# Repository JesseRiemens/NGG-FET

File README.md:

# NGG-FET
Wij gaan de NGG uit de labs in FET's bouwen

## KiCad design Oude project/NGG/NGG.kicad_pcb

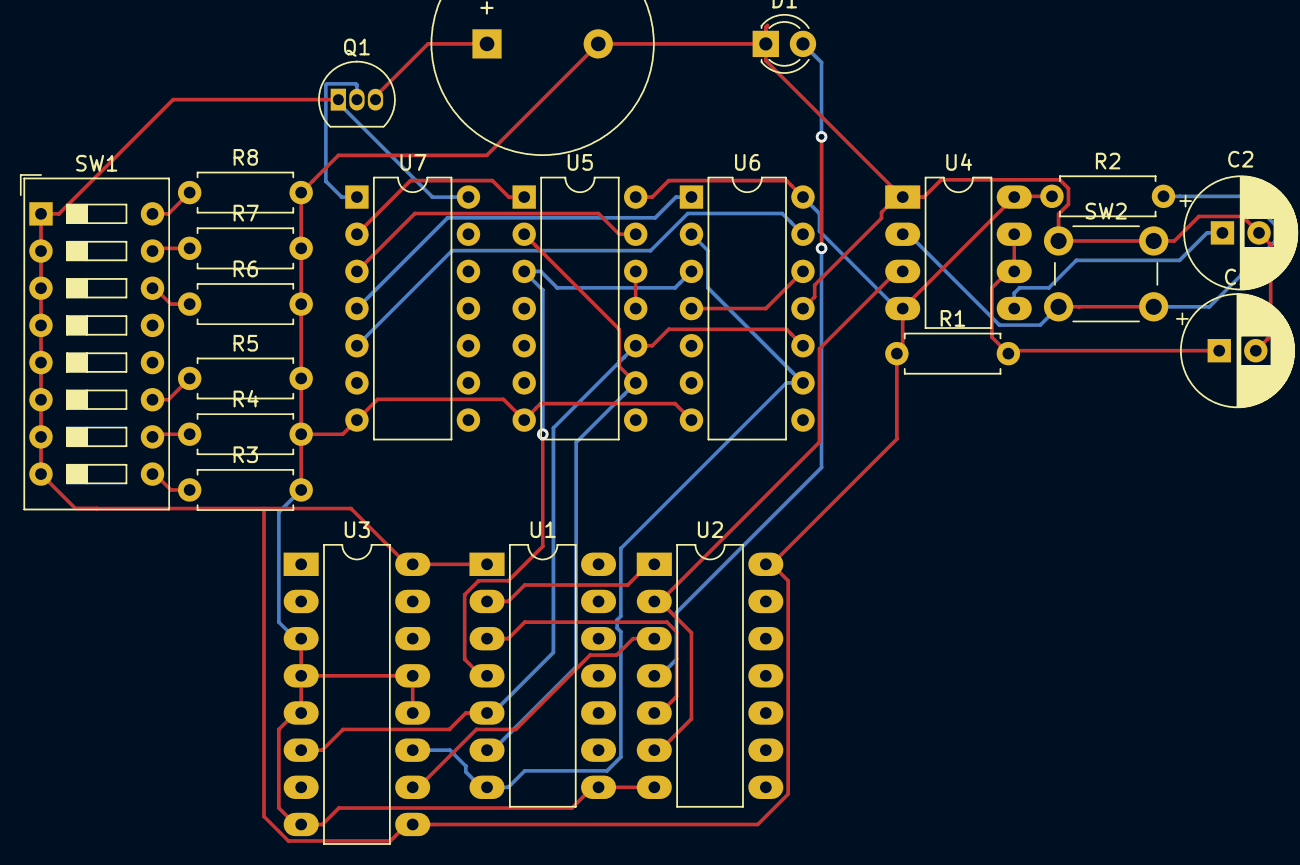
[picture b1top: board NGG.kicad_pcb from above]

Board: 2 copper layers, 22 parts (0 on the bottom side), 28 nets.

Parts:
BZ1: Buzzer; Buzzer_15x7.5RM7.6
C1: C; CP_Radial_D7.5mm_P2.50mm
C2: 10n; CP_Radial_D7.5mm_P2.50mm
D1: LED; LED_D3.0mm_Clear
Q1: BC547; TO-92_Inline
R1, R2: R; R_Axial_DIN0207_L6.3mm_D2.5mm_P7.62mm_Horizontal
R3, R4, R5, R6, R7, R8: 1k; R_Axial_DIN0207_L6.3mm_D2.5mm_P7.62mm_Horizontal
SW1: SW_DIP_x08; SW_DIP_SPSTx08_Slide_9.78x22.5mm_W7.62mm_P2.54mm
SW2: SW_Push; SW_PUSH_6mm
U1: 4049; DIP-14_W7.62mm_LongPads
U2: 4081; DIP-14_W7.62mm_LongPads
U3: 4029; DIP-16_W7.62mm_LongPads
U4: NE555; DIP-8_W7.62mm_LongPads
U5, U6: 4082; DIP-14_W7.62mm
U7: 4072; DIP-14_W7.62mm

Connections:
+5V: Q1.1, R1.1, R2.1, SW1.1, SW1.2, SW1.3, SW1.4, SW1.5, SW1.6, SW1.7, SW1.8, U1.1, U2.14, U3.9, U3.16, U4.4, U4.8, U5.14, U6.14, U7.14
/MUX/H: U6.4, U6.12
/MUX/M: U5.11, U5.12
/MUX/Mo: Q1.2, U7.1
/MUX/S0: U1.7, U3.11, U6.2, U6.9
/MUX/S1: U1.5, U3.6, U5.10, U6.10
/buzzer/BZ: BZ1.1, Q1.3
/comparator/A0: R6.1, SW1.14
/comparator/A1: R7.1, SW1.15
/comparator/A2: R8.1, SW1.16
/comparator/B0: R3.1, SW1.9
/comparator/B1: R4.1, SW1.10
/comparator/B2: R5.1, SW1.11
/comparator/EQ: U1.3, U2.5
/counter/E: U2.3, U3.10
/succesLED/L: D1.2, U2.4
/vergelijkknop/K: U2.2, U2.6, U4.3
GND: BZ1.2, C1.2, C2.2, D1.1, R3.2, R4.2, R5.2, R6.2, R7.2, R8.2, SW2.1, U1.8, U2.7, U3.3, U3.4, U3.5, U3.8, U3.12, U3.13, U4.1, U5.7, U6.7, U6.11, U7.7
unnamed: C1.1, R1.2, U4.6, U4.7
unnamed: C2.1, U4.5
unnamed: R2.2, SW2.2, U4.2
unnamed: U1.2, U2.1
unnamed: U1.4, U5.3, U6.3
unnamed: U1.6, U5.2, U5.9
unnamed: U5.1, U7.2
unnamed: U5.13, U7.3
unnamed: U6.1, U7.4
unnamed: U6.13, U7.5

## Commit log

2018-12-27 init
2018-12-27 Half af
2018-12-27 Alle sheets af
2018-12-27 oude ontwerp en een aantal nieuwe hierarichal pins
2018-12-27 Architectuur af
2018-12-27 NE555 laag
2018-12-27 Deleted laag.pro
2018-12-27 Vertaalcircuit gemaakt
2018-12-27 Templates in losse sheets gezet
2018-12-27 NE555 allemaal af, RC waarden moeten nog
2018-12-27 Push om alles weer recht te krijgen
2018-12-27 NE555 laag ook toegevoegd nu
2018-12-27 layout is a bitch
2018-12-27 Git is a bitch
2018-12-27 Delet .pro
2018-12-27 close off
2018-12-29 Comparator in FETs gevonden! Zie [Oude project/comparator Logisim.circ] en dan 'Schema in FETs'
2018-12-30 Comparator in FETs toegevoegd aan schema, oorspronkelijke Logisim gate design zoveel mogelijk aangehouden
2019-01-09 Mappenstructuur iets aangepast
2019-01-14 Oscilator toegevoegd aan simulatiefolder
